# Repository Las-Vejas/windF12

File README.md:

# windF12
A 12 key F row replacement for people that use 60% keyboards.

***

# What is it?
The windF12 is an F-row for people that use a 60% keyboard or play Minecraft on a MacBook like me.
It's main purpose is to provide the F keys to the user (duh).
It can be used wired or wirelessly depending on what Seeed Xiao you pick.
For wired (or ambitious wireless) users you can also add SK6812MINI-E leds under the keys for cool lighting effects.

***

# Components
This keyboard needs:
- 12 MX switches
- 12 1N4148 SOD-123 diodes
- 1 seeed XIAO
- optionally 12 SK6812MINI-E Leds
- 1 PCB

***

# Images
***
## PCB
<br>
<br>

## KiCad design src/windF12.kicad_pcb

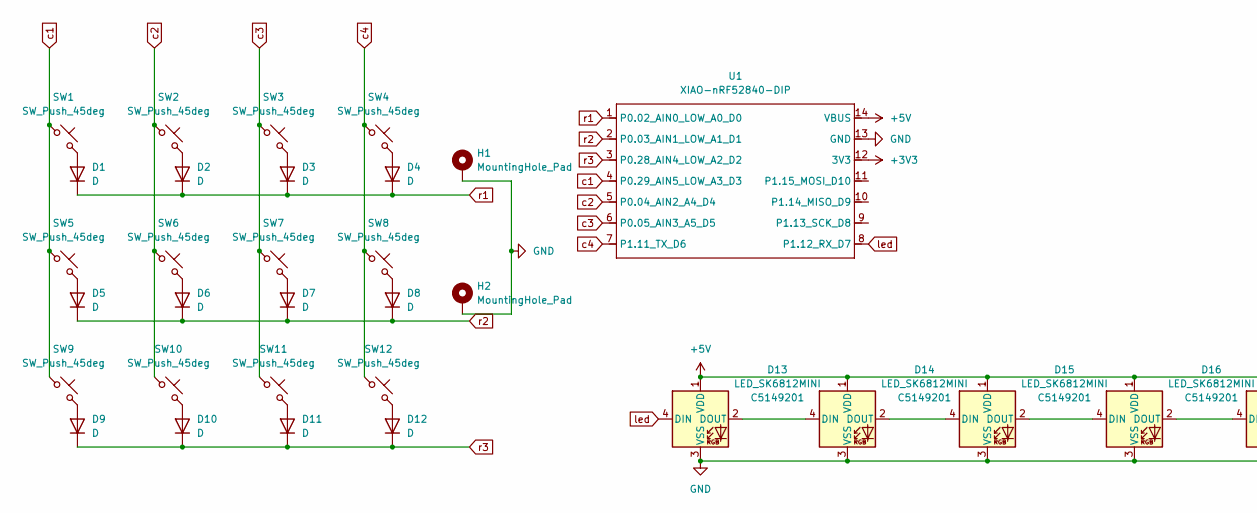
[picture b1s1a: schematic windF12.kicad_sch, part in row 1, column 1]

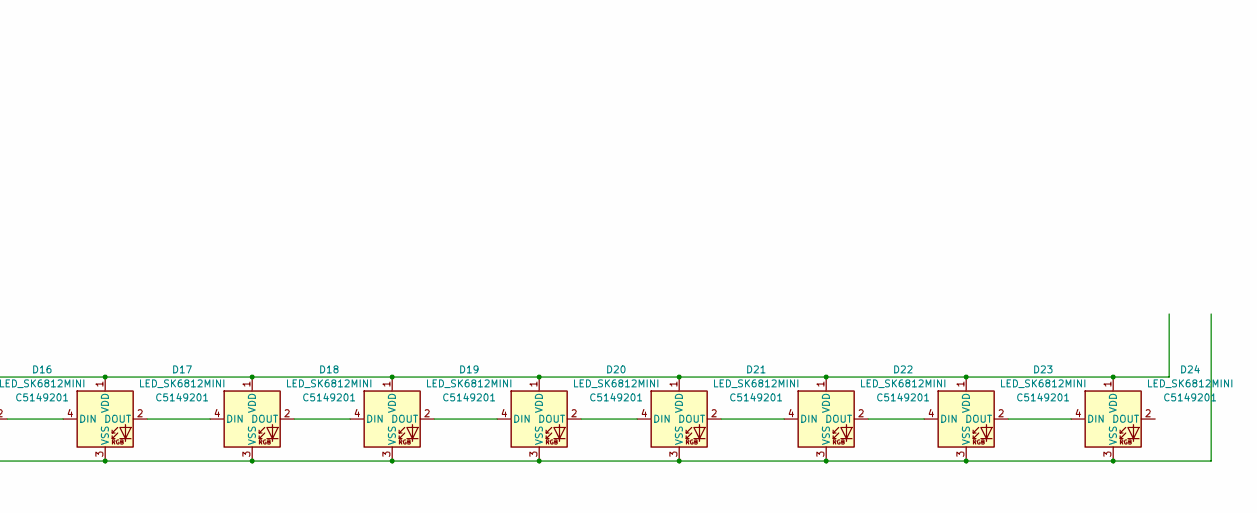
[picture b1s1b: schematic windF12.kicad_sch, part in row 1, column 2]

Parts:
D1, D2, D3, D4, D5, D6, D7, D8, D9, D10, D11, D12: D; Diode_SOD-123
D13, D14, D15, D16, D17, D18, D19, D20, D21, D22, D23, D24: LED_SK6812MINI; LCSC C5149201
H1, H2: MountingHole_Pad; MountingHole_2.2mm_M2_Pad
SW1, SW2, SW3, SW4, SW5, SW6, SW7, SW8, SW9, SW10, SW11, SW12: SW_Push_45deg; SW_Cherry_MX_1.00u_PCB
U1: XIAO-nRF52840-DIP

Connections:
+3V3: U1.12 (3V3)
+5V: D13.1 (VDD), D14.1 (VDD), D15.1 (VDD), D16.1 (VDD), D17.1 (VDD), D18.1 (VDD), D19.1 (VDD), D20.1 (VDD), D21.1 (VDD), D22.1 (VDD), D23.1 (VDD), D24.1 (VDD), U1.14 (VBUS)
GND: D13.3 (VSS), D14.3 (VSS), D15.3 (VSS), D16.3 (VSS), D17.3 (VSS), D18.3 (VSS), D19.3 (VSS), D20.3 (VSS), D21.3 (VSS), D22.3 (VSS), D23.3 (VSS), D24.3 (VSS), H1.1, H2.1, U1.13 (GND)
unnamed: D1.2 (A), SW1.2
unnamed: D2.2 (A), SW2.2
unnamed: D3.2 (A), SW3.2
unnamed: D4.2 (A), SW4.2
unnamed: D5.2 (A), SW5.2
unnamed: D6.2 (A), SW6.2
unnamed: D7.2 (A), SW7.2
unnamed: D8.2 (A), SW8.2
unnamed: D9.2 (A), SW9.2
unnamed: D10.2 (A), SW10.2
unnamed: D11.2 (A), SW11.2
unnamed: D12.2 (A), SW12.2
unnamed: D13.2 (DOUT), D14.4 (DIN)
unnamed: D14.2 (DOUT), D15.4 (DIN)
unnamed: D15.2 (DOUT), D16.4 (DIN)
unnamed: D16.2 (DOUT), D17.4 (DIN)
unnamed: D17.2 (DOUT), D18.4 (DIN)
unnamed: D18.2 (DOUT), D19.4 (DIN)
unnamed: D19.2 (DOUT), D20.4 (DIN)
unnamed: D20.2 (DOUT), D21.4 (DIN)
unnamed: D21.2 (DOUT), D22.4 (DIN)
unnamed: D22.2 (DOUT), D23.4 (DIN)
unnamed: D23.2 (DOUT), D24.4 (DIN)
c1: SW1.1, SW5.1, SW9.1, U1.4 (P0.29_AIN5_LOW_A3_D3)
c2: SW2.1, SW6.1, SW10.1, U1.5 (P0.04_AIN2_A4_D4)
c3: SW3.1, SW7.1, SW11.1, U1.6 (P0.05_AIN3_A5_D5)
c4: SW4.1, SW8.1, SW12.1, U1.7 (P1.11_TX_D6)
led: D13.4 (DIN), U1.8 (P1.12_RX_D7)
r1: D1.1 (K), D2.1 (K), D3.1 (K), D4.1 (K), U1.1 (P0.02_AIN0_LOW_A0_D0)
r2: D5.1 (K), D6.1 (K), D7.1 (K), D8.1 (K), U1.2 (P0.03_AIN1_LOW_A1_D1)
r3: D9.1 (K), D10.1 (K), D11.1 (K), D12.1 (K), U1.3 (P0.28_AIN4_LOW_A2_D2)

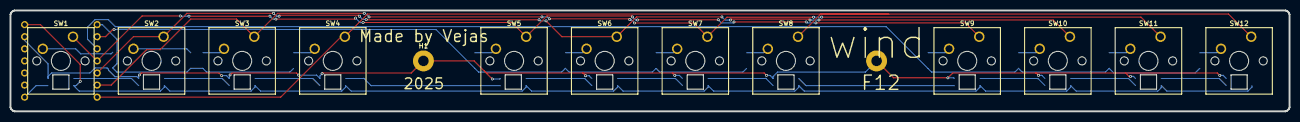
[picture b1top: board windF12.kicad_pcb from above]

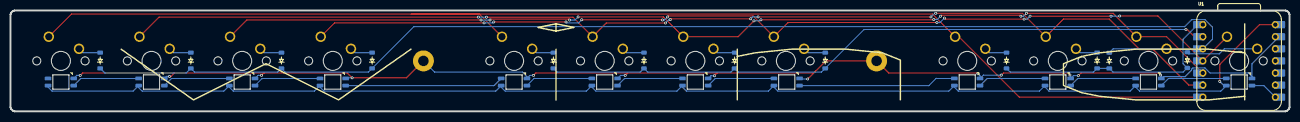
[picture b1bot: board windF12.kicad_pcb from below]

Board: 2 copper layers, 268.9 x 21.2 mm, 39 parts (25 on the bottom side), 33 nets.

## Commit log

2025-09-09 stuff
2025-09-09 loads
